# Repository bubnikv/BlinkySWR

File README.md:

# BlinkySWR

Tiny, cheap, simple, accurate, self powered resistive SWR and power meter for SOTA and back packers

The SWR and power meter is based on a resistive bridge. The forward and reflected power is sampled by an ATTiny13A micro controller. The micro controller is powered by rectifying a tiny fraction of the input power, and the measured SWR and power is displayed by smoothly interpolating 6 high efficiency LED diodes.

Firmware for the ATTiny13A is found [here](firmware), while the simulation and design data is found [here](design).

The following picture shows the initial prototype of BlinkySWR, indicating SWR slightly above 1:1.

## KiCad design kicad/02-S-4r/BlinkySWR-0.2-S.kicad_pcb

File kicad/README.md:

# BlinkySWR PCB board

KiCad PCB layout

* [Schematics rev0.2](02-S-4r/BlinkySWR-0.2-S.pdf)
* [Interactive bom](http://htmlpreview.github.io/?https://github.com/bubnikv/BlinkySWR/blob/master/kicad/02-S-4r/ibom.html)
* [STEP 3D model](02-S-4r/BlinkySWR-0.2-S.step)

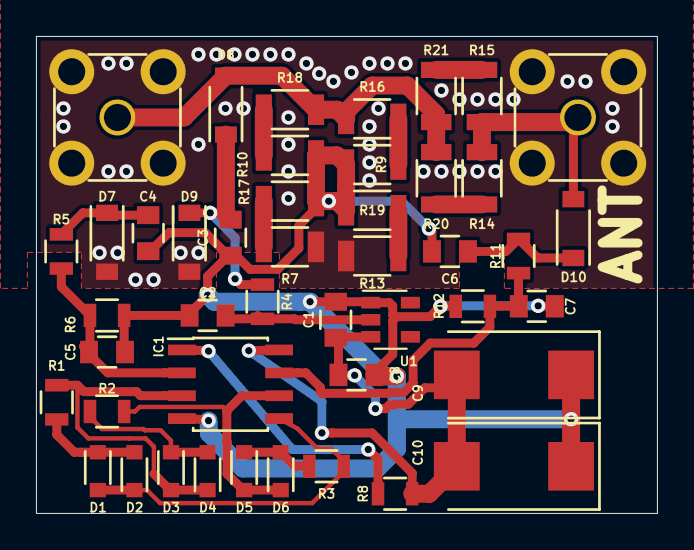
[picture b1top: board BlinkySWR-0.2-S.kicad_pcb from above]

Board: 2 copper layers, 34.5 x 26.5 mm, 45 parts (0 on the bottom side), 24 nets.

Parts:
C1, C2, C8: 100n; C_0805
C3, C4, C5, C6, C7: 1n; C_0805
C9, C10: 480u; Tantalum_Case-D_EIA-7343-31_Reflow
D1, D2, D3, D4, D5, D6: OF-SMD2012HR; D_0805
D7, D8, D9, D10: 1N5711; SOD-123
IC1: ATTINY13A-SSH; SOIC-8_3.9x4.9mm_Pitch1.27mm
J1: SMA-15; SMA-90
J2: SMA-15*; SMA-90
R1, R2, R3: 680R; R_0805
R4: 1k; R_0805
R5, R11: 150k; R_0805
R6, R8, R12: 10k; R_0805
R7, R9, R10, R13, R14, R15, R16, R17, R18, R19, R20, R21: 51R; R_1206
U1: HT7125-1; SOT-23-5

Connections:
+2,5V: C1.2, C8.2, C9.1, C10.1, IC1.8, R8.2, U1.3
FW: C5.2, IC1.2, R5.2, R6.1
GND: C1.1, C2.1, C3.1, C4.2, C5.1, C6.2, C7.1, C8.1, C9.2, C10.2, IC1.4, R6.2, R9.2, R10.2, R12.2, R17.1, R19.1, U1.1
unnamed: C2.2, R4.1, U1.2
unnamed: C3.2, D8.1, D9.1, R4.2
unnamed: C4.1, D7.1, R5.1
unnamed: C6.1, D10.1, R11.1
unnamed: D1.1, D2.2, R1.2
unnamed: D1.2, D2.1, IC1.5, R3.1
unnamed: D3.1, D4.2, R2.2
unnamed: D3.2, D4.1, IC1.3, R1.1
unnamed: D5.1, D6.2, R3.2
unnamed: D5.2, D6.1, IC1.6, R2.1
unnamed: D7.2, D9.2, J1.2, J2.2, R7.2, R13.2
unnamed: D8.2, J1.1, R16.1, R18.1, R20.1, R21.1
unnamed: D10.2, J2.1, R14.2, R15.2
unnamed: IC1.1, R8.1
unnamed: R10.1, R18.2
unnamed: R13.1, R19.2
unnamed: R14.1, R20.2
unnamed: R15.1, R21.2
unnamed: R9.1, R16.2
unnamed: R7.1, R17.2
REF: C7.2, IC1.7, R11.2, R12.1

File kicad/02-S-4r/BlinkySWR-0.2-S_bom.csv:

Comment,Designator,Footprint,LCSC, LCSC, req
"1n","C6,C7,C4,C3,C5","Capacitors_SMD:C_0805","","C15177","100V/X7R/10%"
"100n","C8,C1,C2","Capacitors_SMD:C_0805","","C28233","100V/X7R/10%"
"480u","C9,C10","Capacitors_Tantalum_SMD:Tantalum_Case-D_EIA-7343-31_Reflow","","C106188","Tantal/3,3VDC/package-D/±10%"
"OF-SMD2012HR","D1,D3,D5,D6,D4,D2","Diodes_SMD:D_0805","","C84256*","460÷700mcd/RED/120°/1,8÷2,4V"
"1N5711","D10,D7,D9,D8","Diodes_SMD:SOD-123","","C154843"," 70V/15mA/1ns/333mW/2pF"
"ATTINY13A-SSH","IC1","Housings_SOIC:SOIC-8_3.9x4.9mm_Pitch1.27mm","","C40382*","64B/1kB"
"SMA-15","J1","ok1hra:SMA-90","","","SMA/90°/female/gold-plated"
"SMA-15*","J2","ok1hra:SMA-90","","","SMA/90°/female/gold-plated"
"Mounting_Hole_PAD 3.2mm*","MK1","Mounting_Holes:MountingHole_3.2mm_M3_Pad_Via",""
"680R","R1,R2,R3","Resistors_SMD:R_0805","","C17798","0,125W/1%"
"150k","R11,R5","Resistors_SMD:R_0805","","C17470","0,125W/1%"
"10k","R12,R8,R6","Resistors_SMD:R_0805","","C17414","0,125W/1%"
"1k","R4","Resistors_SMD:R_0805","","C17513","0,125W/1%"
"51R","R9,R10,R13,R7,R14,R15,R16,R18,R17,R19,R20,R21","Resistors_SMD:R_1206","","C18019","0,25W/1%"
"HT7125-1","U1","TO_SOT_Packages_SMD:SOT-23-5","","C259579","4-24V/2,5V/100mVdrop/30mA"

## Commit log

2019-09-29 First public firmware version
2019-09-29 Added ltspice & matlab design files
2019-09-29 Updated README.md design links to relative
2019-09-29 Updated design document
2019-09-29 Updated design document with the reference to Octave / Matlab
2019-09-29 Updated design document with the temp dependence note
2019-09-29 Generated the diode correction curve
2019-09-29 Updated design document with the diode correction curve
2019-09-29 Updated the front page with the links and prototype image
2019-10-02 pcb rev0.1
2019-10-02 fix readme
2019-10-28 Modified the ADC divider to 150kOhm / 10kOhm for lower detector diode loading. Extended the simulations with shorted antenna situations, added the sine wave distortion values read out from the FFT si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
2019-10-29 Reworked the diode compensation curve matlab code, Intel HEX file and C include file are generated for the diode correction
2019-10-29 Updated firmware for lower power consumption by utilizing the sleep modes wherever possible. Updated the matlab generator to produce tables scaled to 16W at 32768, so that the power baragraph calcula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
2019-11-10 Fixed a scaling issue of the diode curve correction
2019-11-12 Fixed a bug in firmware in the diode correction function (data was not pulled correctly from the EEPROM).
    Software SPI for debugging by capturing the SPI data with a logic
    analyzer.
    Debugging of the diode curve correction function to SPI and
    evaluating the data captured from firmware in Octave against the ground
    truth.
2019-11-16 Fixed some bugs, optimized for FLASH consumption
2019-11-17 Refactored for lower FLASH consumption
2019-11-17 Some further optimizations
2019-11-23 Added timeout for the reading to stabilize. Added scaling of the power reading.
2019-11-23 Now the REF is sampled before FWD to avoid glitches on key up
2019-11-23 Fine adjusted timing of the main loop
2019-11-24 Fixed an overflow and division by zero in the SWR calculation code
2019-11-24 Lowered the TIME_TO_SIGNAL_STABLE constant
2019-11-24 Updated design notes (just random notes, not polished yet)
2020-04-12 pcb rev0.2
2020-04-12 manual
2020-04-12 updated manual with schematic
2020-06-25 Added closeup photo of the board
2020-06-25 closeup photo
2020-06-25 updated closeup photo with annotations
2020-06-25 updated manual
